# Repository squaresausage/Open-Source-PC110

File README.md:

# IBM Palm Top PC110

A repository for all the technical details of the PC110

What it includes:

Schematic and PCB layout of the motherboard (based on KiCad)

Schematic and PCB layout of the PSU module (based on KiCad)

Schematic and PCB layout of the Docking Station (based on KiCad)

Schematic and PCB layout of the Modem (based on KiCad)

Schematic and PCB layout of the 16MB RAM Module (based on KiCad)

Flex PCB and PET Schematic and layout of the Keyboard Membrane (based on KiCad)

Optical scans, X-ray images from different PCBs, layers, and chips.

Flash dump of the BIOS and the AT29LV512 (available in only a few models).

Flash dump of M38224M6HP and M38813E4HP.

# How can you help?

Help by reviewing Schematics and PCB layouts to report potential bugs, errors, and issues.

Help to verify the layout and schematic.

Help with finding missing datasheets

Please help us [fund](https://gofund.me/716b7dae) the next iteration of PCBA to test the recreated motherboard.

# Press

Featured on Hack-A-Day: 
- [Reverse Engineering The IBM PC110, One PCB At A Time](https://hackaday.com/2025/04/06/reverse-engineering-the-ibm-pc110-one-pcb-at-a-time/) 

Featured on Taka's blog:
- [PC110 New PSU](https://garakutaen.sakura.ne.jp/misc2/MlogmP3.html#e0318)
- [PC110 PCB Pattern](https://garakutaen.sakura.ne.jp/misc2/MlogmP1.html#e0130)
- [PC110 PCB Layout creation](https://garakutaen.sakura.ne.jp/misc2/MlogmP2.html#e0208)
- [PC110 New Docking Station PCB](https://garakutaen.sakura.ne.jp/misc2/MlogmP3.html#e0324)
- [X-ray photos of the inside of the PC110's LSI](https://garakutaen.sakura.ne.jp/misc2/MlogmP2.html#e0225)

Jeff Geerling's YouTube Channel:
- [Reverse engineering Episode](https://youtu.be/p7IvioiveOo?si=PUlHSzOhwXYEpZJ3&t=217)

LGR YouTube Channel:
- [LGR Vlog: VCFMW20](https://www.youtube.com/watch?v=yIwXQicYClw&t=7595s)

VCFMW20 YouTube Channel:
- [Archaeology of the IBM PC110](https://www.youtube.com/watch?v=8Uja7g9hQlo)

# License

This project is licensed under the Creative Commons Attribution-NonCommercial 4.0 International License (CC BY-NC 4.0).

You are free to:
- Share — copy and redistribute the material in any medium or format
- Adapt — remix, transform, and build upon the material

Under the following terms:
- Attribution — You must give appropriate credit, provide a link to the license, and indicate if changes were made.
- NonCommercial — You may not use the material for commercial purposes.

For full details, see: https://creativecommons.org/licenses/by-nc/4.0/

As the project creator, I reserve the right to use this material commercially or under any other terms.

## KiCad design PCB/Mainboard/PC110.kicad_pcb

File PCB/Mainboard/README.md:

### IBM PC110 PCB redesigned in KiCad

Layer Stack-up

| Index | Layer name | Description  |
| ----- | ---------- | ------------ |
| 1     | FC2        | Top          |
| 2     | FC1        | Signal       |
| 3     | IP1        | Power        |
| 4     | IC1        | Signal       |
| 5     | IC2        | Signal       |
| 6     | IC3        | Signal       |
| 7     | IC4        | Signal       |
| 8     | IP2        | Ground       |
| 9     | BC1        | Signal       |
| 10    | BC2        | Bottom       |

Here is a render of FC1, IC1, IC2, IC3, IC4 and BC1 together:

And here is a render of FC2, FC1, IC1, IC2, IC3, IC4, BC1 and BC2 together:

And here are 3D renders from the top and bottom layers:

Top side:

Real picture:

3D render:

Bottom side:

Real picture:

3D render:

Schematic Organization
-----
Here is a view of the schematic hierarchy:

Description of each schematic sheet

| Page | Sheet Name | Description  |
| ---- | ---------- | ------------ |
| 1     | Root      | Index of all sheets  |
| 2     | Clock | Local Oscillator and Clock Distribution Tree |
| 3     | Processor  | CPU and Debug pins |
| 4     | Chipset  | SCAMP IV chipset North Bridge |
| 5     | VGA | Video Controller and Video RAM       |
| 6     | Memory  | Internal Memory Back and RAM Expansion Connector |
| 7     | ROM | BIOS and Font Maskrom |
| 8     | ASIC | Bowman and Pluto, South Bridge |
| 9     | Super IO | FDD, Parallel and Serial ports |
| 10    | Power | Power Controller, PSU Connector, Status LCD, and Touchpad |
| 11    | PCMICA  | PCMCIA Controller and Related Power Controller |
| 12    | Audio | Sound Controller, FM Synthesizer and related analogue AMP |
| 13    | Storage | Internal Flash memory, CF card interface |
| 14    | Keyboard | Keyboard controller, Trackpoint controller |
| 15    | Docking | Docking Station, Internal Modem Connector |

Combined Schematic on one page
-----
Here is a combined schematic on a single page, just for the appreciation of its complexity.

Aside from the fun aspect of combining all the sheets on a single one, there is a practical use that is related to the recreation of the schematic from a given PCB. On KiCad, you cannot select components from different sheets simultaneously. Therefore, you cannot highlight all the components on your schematic at once to see if there is still any component on the layout that is not mapped. However, with a single sheet compilation, you can do that (as it is shown below) and you can go back to the layout and see if there is still any component that is left behind. Below you can see that, on the layout for both top and bottom layers, all the components are highlighted.

All components selected on the schematic

Highlighted components on the top layer

Highlighted components on the bottom layer

And here is the SVG version of the single-sheet 

PCB statistics report
=====================

Board
-----
- Width: 150.0500 mm
- Height: 107.3513 mm
- Area: 12400.2967 mm²

Pads
----
- Through hole: 29
- SMD: 4860
- Total: 4889

Vias
----
- Through vias: 2407
- Blind/buried: 3684
- Total: 6091

Components
----------

|              | Front Side | Back Side | Total |
|--------------|------------|-----------|-------|
|THT:          |          1 |         0 |     1 |
|SMD:          |        486 |       446 |   932 |
|Unspecified:  |          0 |         1 |     1 |
|Total:        |        487 |       447 |   934 |

Drill holes
-----------

| Count | Shape |    X Size |    Y Size | Plated | Via/Pad | Start Layer | Stop Layer |
|-------|-------|-----------|-----------|--------|---------|-------------|------------|
|  1950 | Round | 0.2000 mm | 0.2000 mm |    PTH |     Via |         BC1 |        BC2 |
|  1914 | Round | 0.2000 mm | 0.2000 mm |    PTH |     Via |         FC2 |        BC2 |
|  1730 | Round | 0.2000 mm | 0.2000 mm |    PTH |     Via |         FC2 |        FC1 |
|   493 | Round | 0.3000 mm | 0.3000 mm |    PTH |     Via |         FC2 |        BC2 |
|    20 | Round | 0.8000 mm | 0.8000 mm |    PTH |     Pad |         FC2 |        BC2 |
|     5 | Round | 1.0000 mm | 1.0000 mm |    PTH |     Pad |         FC2 |        BC2 |
|     2 |  Slot | 2.0000 mm | 0.9000 mm |    PTH |     Pad |         FC2 |        BC2 |
|     2 |  Slot | 0.8000 mm | 2.2000 mm |    PTH |     Pad |         FC2 |        BC2 |
|     2 | Round | 0.2000 mm | 0.2000 mm |    PTH |     Via |         FC2 |        IC2 |
|     1 | Round | 0.2000 mm | 0.2000 mm |    PTH |     Via |         FC2 |        IC1 |
|     1 | Round | 0.3000 mm | 0.3000 mm |    PTH |     Via |         BC1 |        BC2 |
|     1 | Round | 0.2000 mm | 0.2000 mm |    PTH |     Via |         IP1 |        BC2 |

Here is a cross section of the PCB stack-up

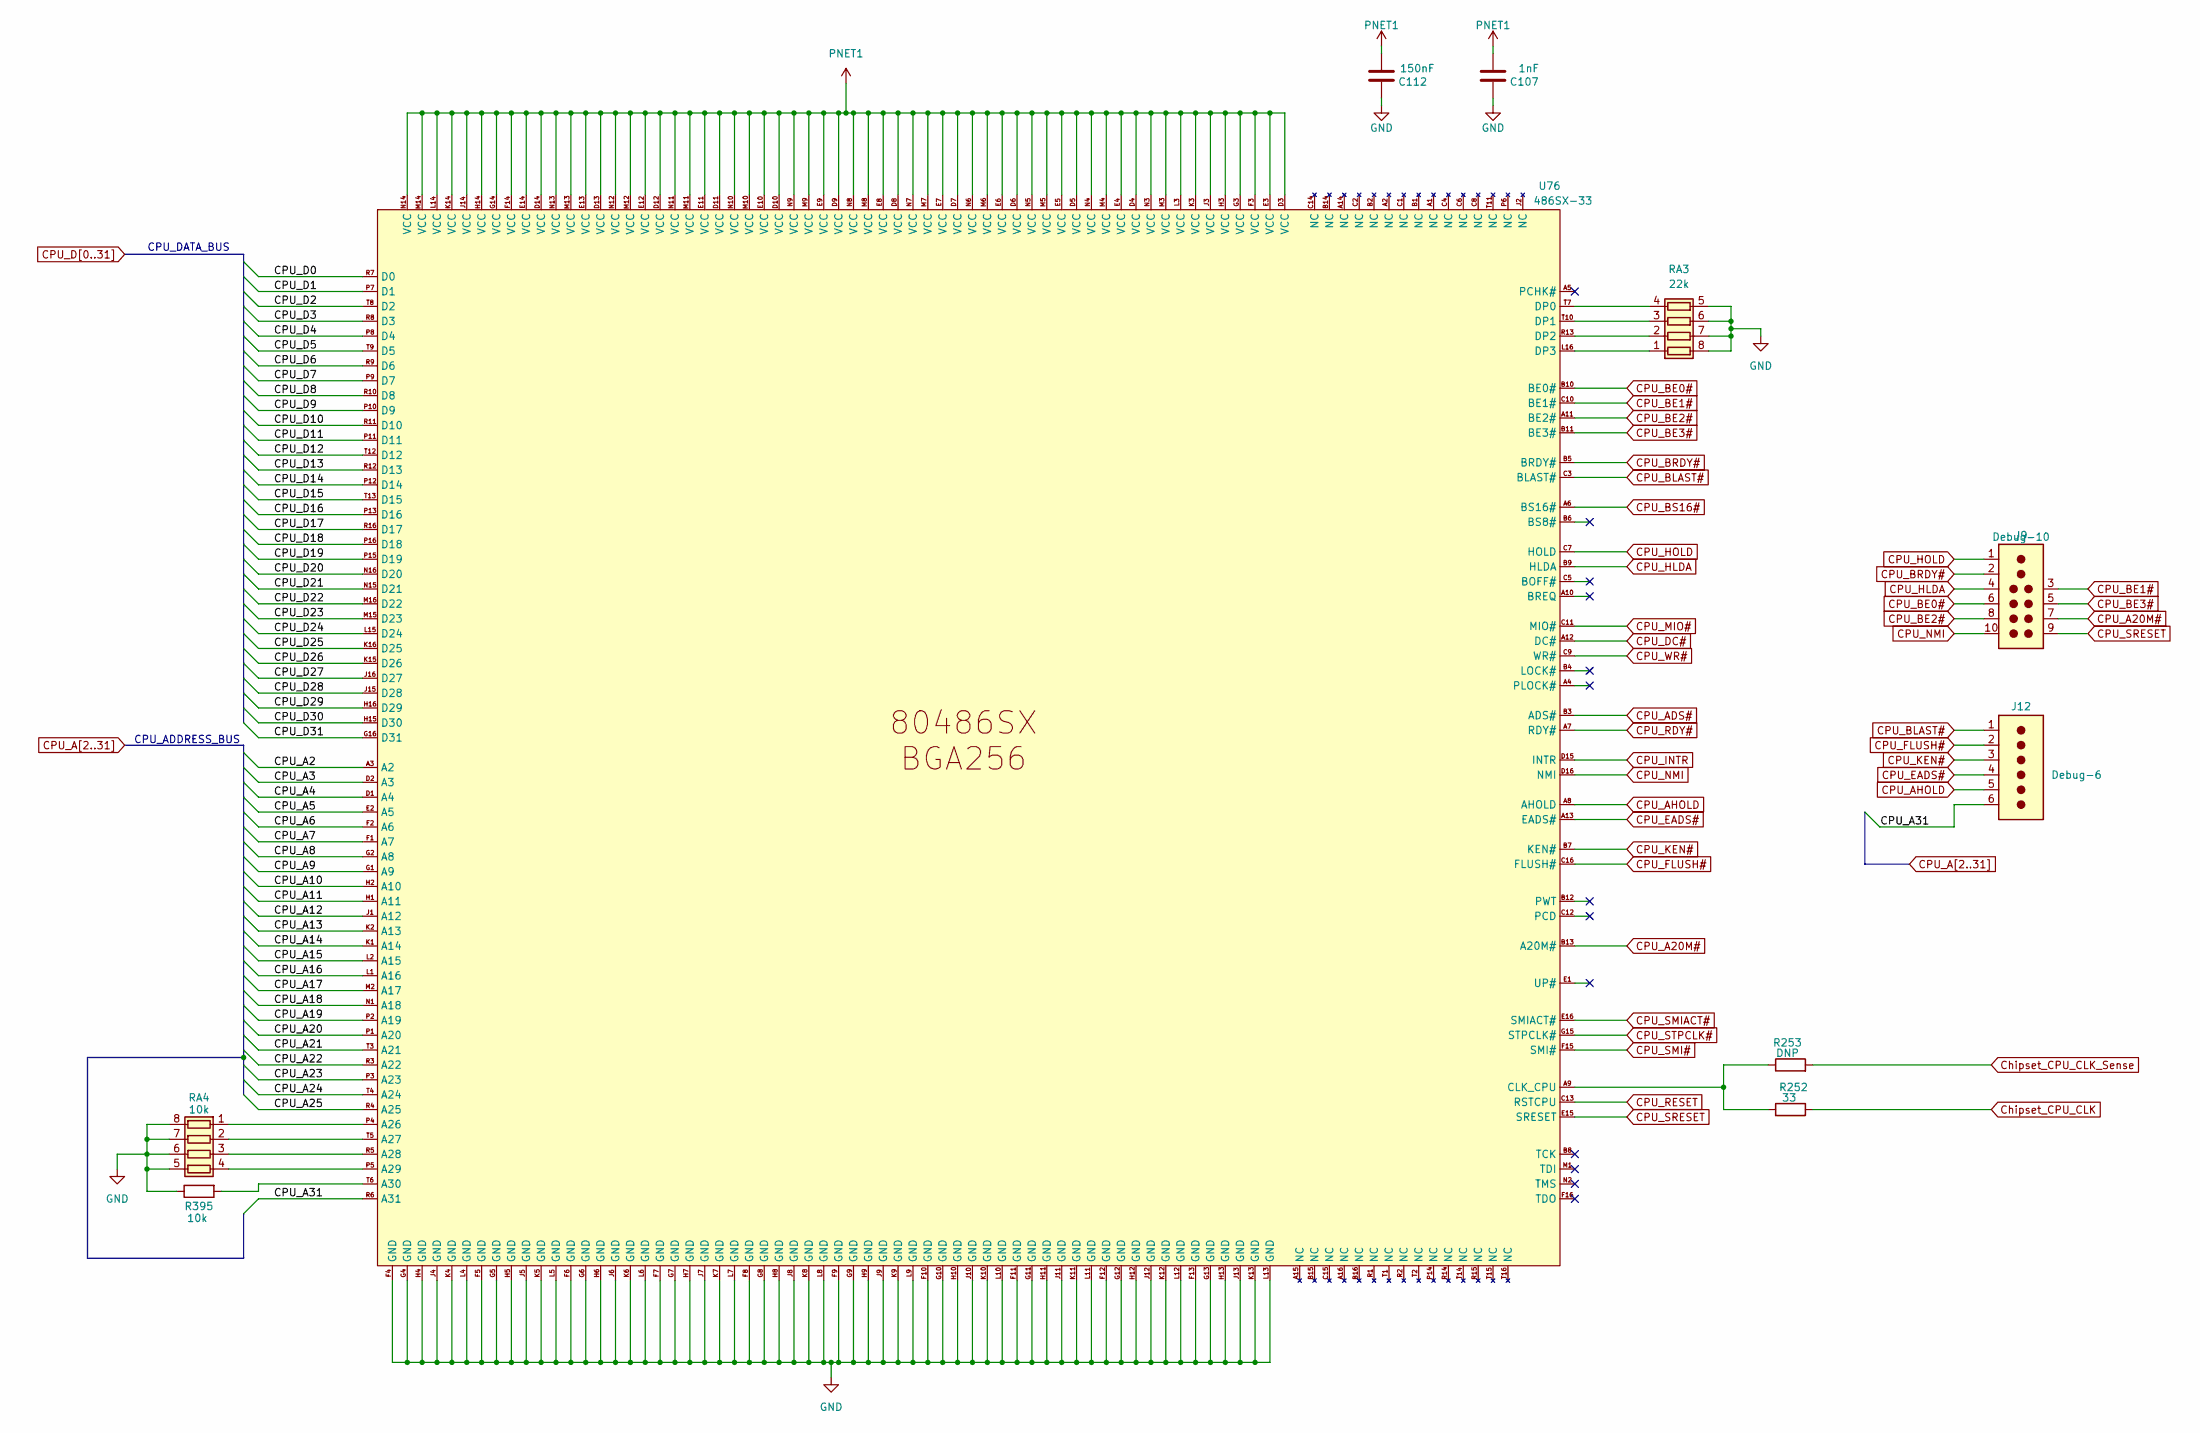
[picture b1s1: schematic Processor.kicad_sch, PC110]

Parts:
C107: 1nF; C_0402_1005Metric
C112: 150nF; C_0402_1005Metric
J9: Debug-10
J12: Debug-6
R252: 33; R_0402_1005Metric
R253: DNP; R_0402_1005Metric
R395: 10k; R_0402_1005Metric
RA3: 22k; R-array
RA4: 10k; R-array
U76: 486SX-33; BGA-256

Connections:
CPU_A2: U76.A3 (A2); also elsewhere on the board
CPU_A3: U76.D2 (A3); also elsewhere on the board
CPU_A4: U76.D1 (A4); also elsewhere on the board
CPU_A5: U76.E2 (A5); also elsewhere on the board
CPU_A6: U76.F2 (A6); also elsewhere on the board
CPU_A7: U76.F1 (A7); also elsewhere on the board
CPU_A8: U76.G2 (A8); also elsewhere on the board
CPU_A9: U76.G1 (A9); also elsewhere on the board
CPU_A10: U76.H2 (A10); also elsewhere on the board
CPU_A11: U76.H1 (A11); also elsewhere on the board
CPU_A12: U76.J1 (A12); also elsewhere on the board
CPU_A13: U76.K2 (A13); also elsewhere on the board
CPU_A14: U76.K1 (A14); also elsewhere on the board
CPU_A15: U76.L2 (A15); also elsewhere on the board
CPU_A16: U76.L1 (A16); also elsewhere on the board
CPU_A17: U76.M2 (A17); also elsewhere on the board
CPU_A18: U76.N1 (A18); also elsewhere on the board
CPU_A19: U76.P2 (A19); also elsewhere on the board
CPU_A20: U76.P1 (A20); also elsewhere on the board
CPU_A20M#: J9.7, U76.B13 (A20M#); also elsewhere on the board
CPU_A21: U76.T3 (A21); also elsewhere on the board
CPU_A22: U76.R3 (A22); also elsewhere on the board
CPU_A23: U76.P3 (A23); also elsewhere on the board
CPU_A24: U76.T4 (A24); also elsewhere on the board
CPU_A25: U76.R4 (A25); also elsewhere on the board
CPU_A31: J12.6, U76.R6 (A31); also elsewhere on the board
CPU_ADS#: U76.B3 (ADS#); also elsewhere on the board
CPU_AHOLD: J12.5, U76.A8 (AHOLD); also elsewhere on the board
CPU_BE0#: J9.6, U76.B10 (BE0#); also elsewhere on the board
CPU_BE1#: J9.3, U76.C10 (BE1#); also elsewhere on the board
CPU_BE2#: J9.8, U76.A11 (BE2#); also elsewhere on the board
CPU_BE3#: J9.5, U76.B11 (BE3#); also elsewhere on the board
CPU_BLAST#: J12.1, U76.C3 (BLAST#); also elsewhere on the board
CPU_BRDY#: J9.2, U76.B5 (BRDY#); also elsewhere on the board
CPU_BS16#: U76.A6 (BS16#); also elsewhere on the board
CPU_D0: U76.R7 (D0); also elsewhere on the board
CPU_D1: U76.P7 (D1); also elsewhere on the board
CPU_D2: U76.T8 (D2); also elsewhere on the board
CPU_D3: U76.R8 (D3); also elsewhere on the board
CPU_D4: U76.P8 (D4); also elsewhere on the board
CPU_D5: U76.T9 (D5); also elsewhere on the board
CPU_D6: U76.R9 (D6); also elsewhere on the board
CPU_D7: U76.P9 (D7); also elsewhere on the board
CPU_D8: U76.R10 (D8); also elsewhere on the board
CPU_D9: U76.P10 (D9); also elsewhere on the board
CPU_D10: U76.R11 (D10); also elsewhere on the board
CPU_D11: U76.P11 (D11); also elsewhere on the board
CPU_D12: U76.T12 (D12); also elsewhere on the board
CPU_D13: U76.R12 (D13); also elsewhere on the board
CPU_D14: U76.P12 (D14); also elsewhere on the board
CPU_D15: U76.T13 (D15); also elsewhere on the board
CPU_D16: U76.P13 (D16); also elsewhere on the board
CPU_D17: U76.R16 (D17); also elsewhere on the board
CPU_D18: U76.P16 (D18); also elsewhere on the board
CPU_D19: U76.P15 (D19); also elsewhere on the board
CPU_D20: U76.N16 (D20); also elsewhere on the board
CPU_D21: U76.N15 (D21); also elsewhere on the board
CPU_D22: U76.M16 (D22); also elsewhere on the board
CPU_D23: U76.M15 (D23); also elsewhere on the board
CPU_D24: U76.L15 (D24); also elsewhere on the board
CPU_D25: U76.K16 (D25); also elsewhere on the board
CPU_D26: U76.K15 (D26); also elsewhere on the board
CPU_D27: U76.J16 (D27); also elsewhere on the board
CPU_D28: U76.J15 (D28); also elsewhere on the board
CPU_D29: U76.H16 (D29); also elsewhere on the board
CPU_D30: U76.H15 (D30); also elsewhere on the board
CPU_D31: U76.G16 (D31); also elsewhere on the board
CPU_DC#: U76.A12 (DC#); also elsewhere on the board
CPU_EADS#: J12.4, U76.A13 (EADS#); also elsewhere on the board
CPU_FLUSH#: J12.2, U76.C16 (FLUSH#); also elsewhere on the board
CPU_HLDA: J9.4, U76.B9 (HLDA); also elsewhere on the board
CPU_HOLD: J9.1, U76.C7 (HOLD); also elsewhere on the board
CPU_INTR: U76.D15 (INTR); also elsewhere on the board
CPU_KEN#: J12.3, U76.B7 (KEN#); also elsewhere on the board
CPU_MIO#: U76.C11 (MIO#); also elsewhere on the board
CPU_NMI: J9.10, U76.D16 (NMI); also elsewhere on the board
CPU_RDY#: U76.A7 (RDY#); also elsewhere on the board
CPU_RESET: U76.C13 (RSTCPU); also elsewhere on the board
CPU_SMI#: U76.F15 (SMI#); also elsewhere on the board
CPU_SMIACT#: U76.E16 (SMIACT#); also elsewhere on the board
CPU_SRESET: J9.9, U76.E15 (SRESET); also elsewhere on the board
CPU_STPCLK#: U76.G15 (STPCLK#); also elsewhere on the board
CPU_WR#: U76.C9 (WR#); also elsewhere on the board
Chipset_CPU_CLK: R252.1; also elsewhere on the board
Chipset_CPU_CLK_Sense: R253.2; also elsewhere on the board
unnamed: RA3.1 (R1.1), U76.L16 (DP3)
unnamed: RA3.2 (R2.1), U76.R13 (DP2)
unnamed: RA3.3 (R3.1), U76.T10 (DP1)
unnamed: RA3.4 (R4.1), U76.T7 (DP0)
unnamed: RA4.1 (R1.1), U76.P4 (A26)
unnamed: RA4.2 (R2.1), U76.T5 (A27)
unnamed: RA4.3 (R3.1), U76.R5 (A28)
unnamed: RA4.4 (R4.1), U76.P5 (A29)
unnamed: R395.2, U76.T6 (A30)
unnamed: R252.2, R253.1, U76.A9 (CLK_CPU)
PNET1: C107.2, C112.2, U76.D3 (VCC), U76.D4 (VCC), U76.D5 (VCC), U76.D6 (VCC), U76.D7 (VCC), U76.D8 (VCC), U76.D9 (VCC), U76.D10 (VCC), U76.D11 (VCC), U76.D12 (VCC), U76.D13 (VCC), U76.D14 (VCC), U76.E3 (VCC), U76.E4 (VCC), U76.E5 (VCC), U76.E6 (VCC), U76.E7 (VCC), U76.E8 (VCC), U76.E9 (VCC), U76.E10 (VCC), U76.E11 (VCC), U76.E12 (VCC), U76.E13 (VCC), U76.E14 (VCC), U76.F3 (VCC), U76.F14 (VCC), U76.G3 (VCC), U76.G14 (VCC), U76.H3 (VCC), U76.H14 (VCC), U76.J3 (VCC), U76.J14 (VCC), U76.K3 (VCC), U76.K14 (VCC), U76.L3 (VCC), U76.L14 (VCC), U76.M3 (VCC), U76.M4 (VCC), U76.M5 (VCC), U76.M6 (VCC), U76.M7 (VCC), U76.M8 (VCC), U76.M9 (VCC), U76.M10 (VCC), U76.M11 (VCC), U76.M12 (VCC), U76.M13 (VCC), U76.M14 (VCC), U76.N3 (VCC), U76.N4 (VCC), U76.N5 (VCC), U76.N6 (VCC), U76.N7 (VCC), U76.N8 (VCC), U76.N9 (VCC), U76.N10 (VCC), U76.N11 (VCC), U76.N12 (VCC), U76.N13 (VCC), U76.N14 (VCC); also elsewhere on the board

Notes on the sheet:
CPU_ADDRESS_BUS
CPU_DATA_BUS
